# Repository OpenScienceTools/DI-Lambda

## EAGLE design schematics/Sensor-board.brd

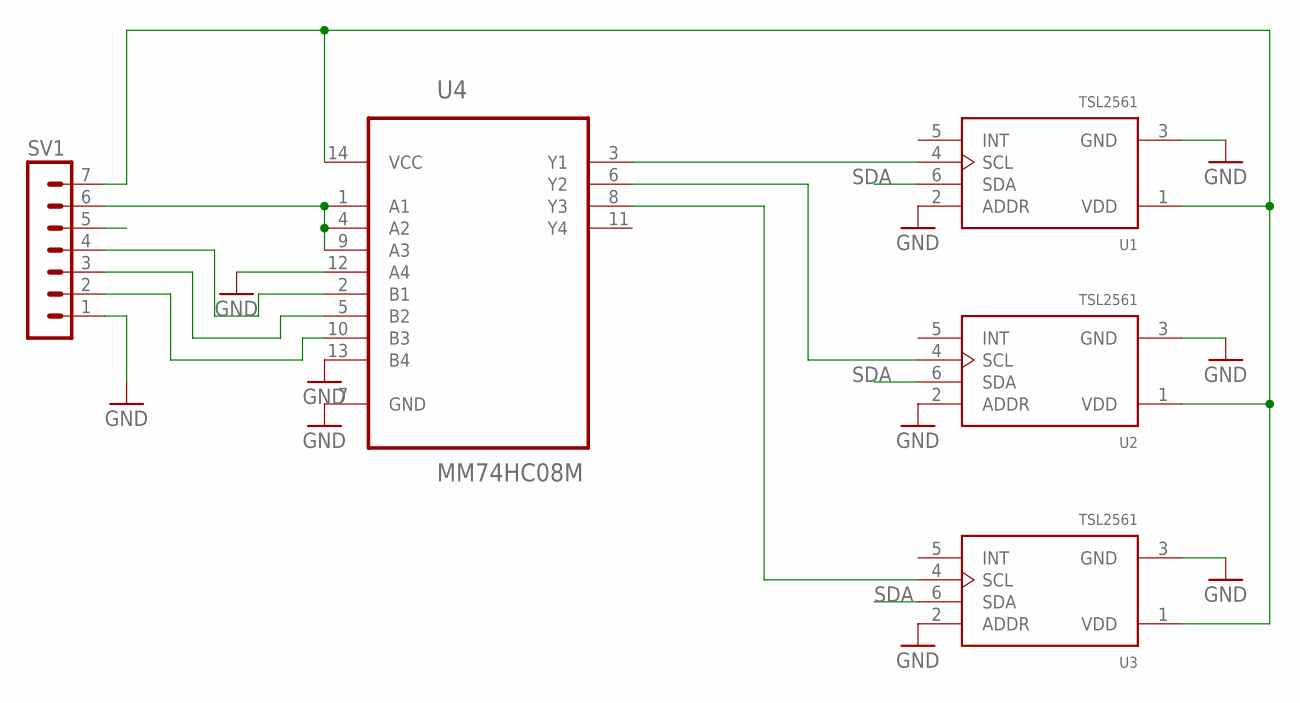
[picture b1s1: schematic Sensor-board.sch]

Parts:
SV1: MA07-1
U1, U2, U3: TSL2561; TMB-6
U4: MM74HC08M; SOIC127P600X175-14N

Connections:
GND: SV1.1, U1.2 (ADDR), U1.3 (GND), U2.2 (ADDR), U2.3 (GND), U3.2 (ADDR), U3.3 (GND), U4.7 (GND), U4.12 (A4), U4.13 (B4)
unnamed: U2.4 (SCL), U4.6 (Y2)
unnamed: U3.4 (SCL), U4.8 (Y3)
unnamed: U1.4 (SCL), U4.3 (Y1)
unnamed: SV1.4, U4.2 (B1)
unnamed: SV1.3, U4.5 (B2)
unnamed: SV1.2, U4.10 (B3)
SCL: SV1.6, U4.1 (A1), U4.4 (A2), U4.9 (A3)
SDA: SV1.5, U1.6 (SDA), U2.6 (SDA), U3.6 (SDA)
VCC: SV1.7, U1.1 (VDD), U2.1 (VDD), U3.1 (VDD), U4.14 (VCC)

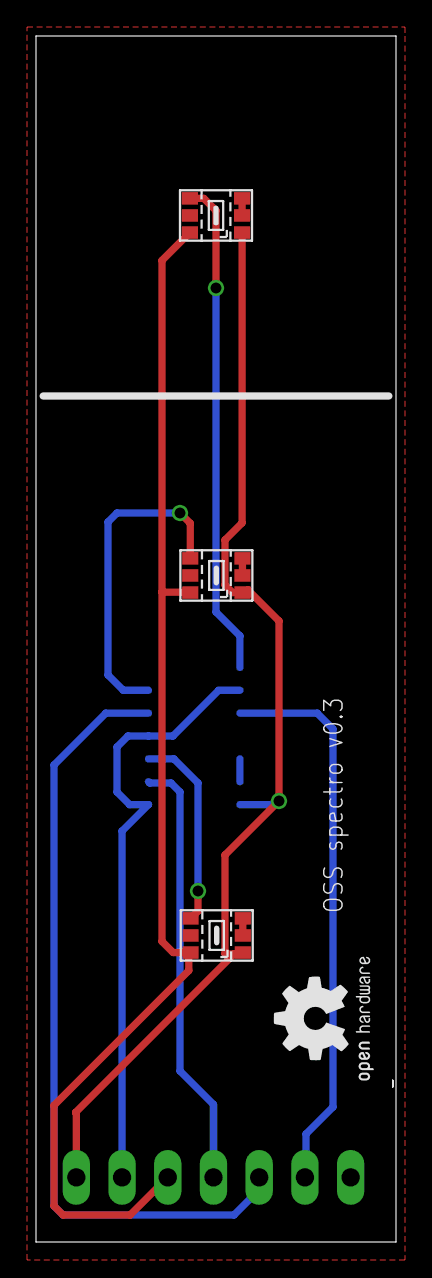
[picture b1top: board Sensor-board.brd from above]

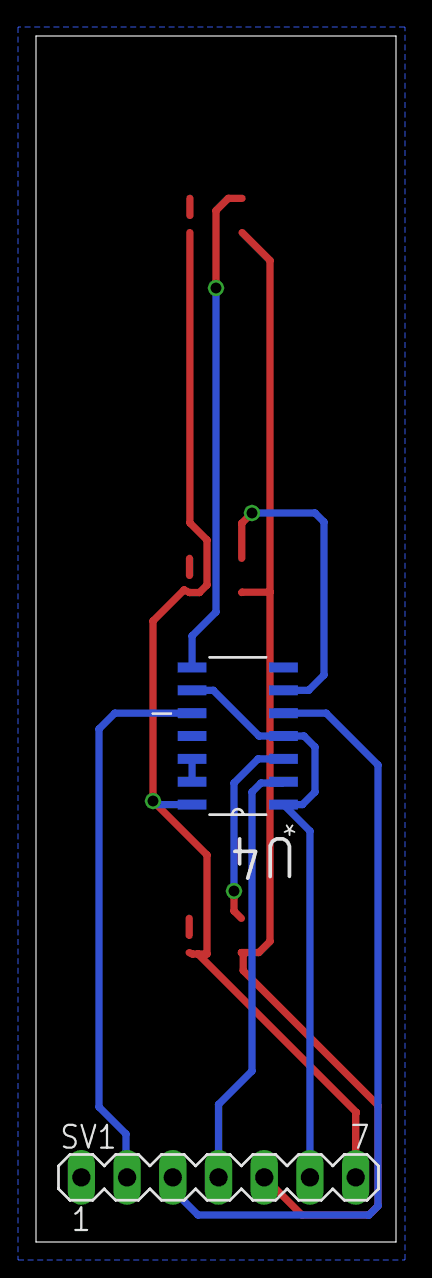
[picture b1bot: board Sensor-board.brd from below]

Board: 2 copper layers, 20.0 x 67.0 mm, 6 parts (2 on the bottom side), 10 nets.

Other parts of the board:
U$1: OSHW2

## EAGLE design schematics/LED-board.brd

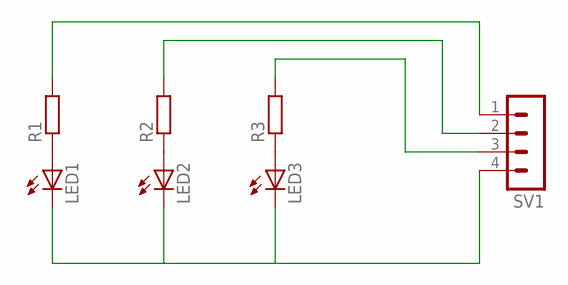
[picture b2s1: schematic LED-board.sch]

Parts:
LED1, LED2, LED3: LED5MM
R1, R2, R3: R0207/10; 0207/10
SV1: MA04-1

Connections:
GND: LED1.K (C), LED2.K (C), LED3.K (C), SV1.4
unnamed: LED1.A, R1.1
unnamed: LED2.A, R2.1
unnamed: LED3.A, R3.1
unnamed: R1.2, SV1.1
unnamed: R2.2, SV1.2
unnamed: R3.2, SV1.3

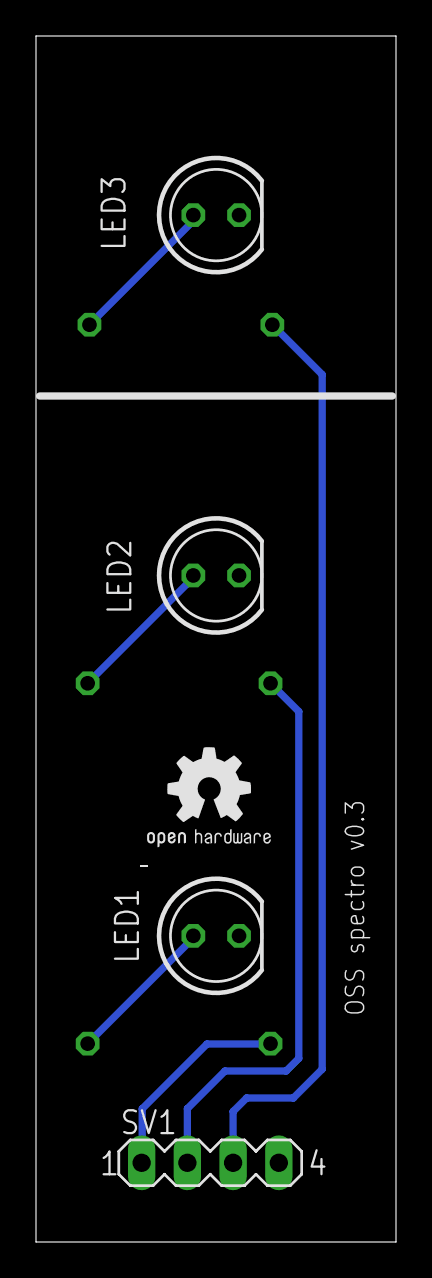
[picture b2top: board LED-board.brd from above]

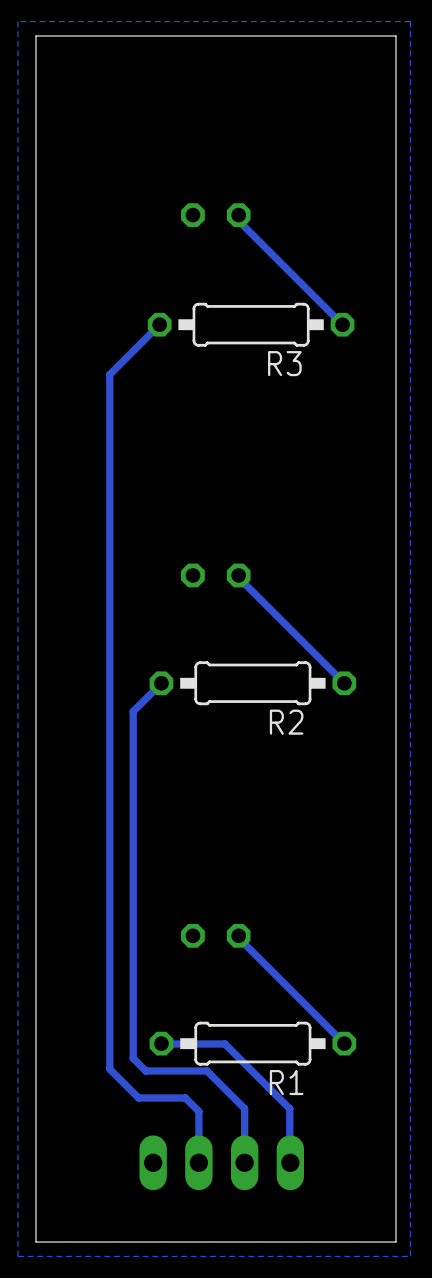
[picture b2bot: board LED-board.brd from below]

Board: 2 copper layers, 20.0 x 67.0 mm, 8 parts (3 on the bottom side), 7 nets.

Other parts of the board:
U$1: OSHW2

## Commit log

2014-12-25 Some unfinished schematics
2014-12-25 Add some unfinished parts
2014-12-25 Finish up the fist version, excluding the top part
2014-12-25 Render assembly
2014-12-25 Some progress with schematics
2014-12-25 Add stl exports for 3d printing
2014-12-25 Add pdf files for preview
2014-12-25 Add the top part of the box
2014-12-25 Some updates
2014-12-30 More detailed leds on the lead board
2014-12-30 Second version base part
2014-12-30 Second version of the top part
2014-12-30 stl export for the second version top part
2014-12-30 Add cuvette model
2014-12-31 Smaller motherboard, dimension changes to allow some gap betwen parts
2014-12-31 Add motherboard sketch to Render
2014-12-31 Add the cover part
2014-12-31 Accomodate top part for the cover
2014-12-31 Some changes here and there
2014-12-31 Some changes
2015-01-06 Reworked some schematics
2015-01-06 Rework bottom part to optimize size
2015-01-06 Bottom part sketch
2015-01-07 Actually add the base drender
2015-01-07 Finish the size rework
2015-01-11 Add assembly render pictures
2015-01-13 A last-minute commit before leaving for Grenoble
2015-02-03 New partially laser-cut version
2015-02-03 Add the laser-cut Autocad parts
2015-02-03 Just a quick fix
2015-06-03 Add the test rig, lots of other changes
2015-06-03 Spirulina prototype
2015-06-12 Start with the new slim design
2015-06-16 Some changes to parts used in the London event
2015-06-16 Add the distance test rig base
2015-06-16 Convert laser-cut parts to AI
2015-06-24 DI-Lambda Paris
2015-06-24 Align things to verify board dimensions
2015-06-29 DIL-Paris takes shape
2015-07-14 DI-Lambda Luna
2015-07-19 Steps towards a screwless case for DI-Lambda Paris
2015-07-19 Large git repo cleanup - move files around, remove unused
2015-07-19 Large git repo cleanup - update assemblies
2015-07-20 Spirulina: Add missing 1mm slit
2015-07-20 Paris: First attempt on screwless box
2015-07-21 Clean up the screwless box design
2015-08-01 Update screwless box design and rework the controller board
2015-08-05 Assemblies for each device, to make nice pictures
2015-08-07 Remove old schematics
2015-08-15 New slit inserts for the test rig
2015-08-19 All new schematics and boards
    - Reworked with KiCad
    - Includes:
    -- 2 Microcontroller board with Arduino Nano
    -- Microcontroller board with the Silabs EFM8UB10F8G MCU
    -- 1cm LED board
    -- 1cm sensor board with TSL2561
2015-08-20 schematics: update LED connections, use 4x resistor arrays
2016-03-11 Large amount of random changes
2016-05-24 Update the DI-Lambda Paris design: PCB pinholes, easier board removal, larger cuvette holes
2016-05-24 Add missing files for the nice-looking DI-Lambd Paris v2 version (cancelled)
2016-05-24 Add DI-Lambda v1 based on SZOMK AK-C-C10 profile (cancelled)
2016-05-24 Add DI-Lambda v1 based on SZOMK AK-C-C39 profile
2016-05-24 Schematics update
2016-05-24 DI-Lambda Paris: Fix core and box mismatches
2016-05-24 Schamatics: Add the pinhole board KiCad files
2016-07-03 Electronics update for V1
2016-07-03 Update V1 mechanical parts

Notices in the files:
parts and their libraries:
eagle-library-edeca.net-v5: This is v1 and is licensed under the Creative Commons (Attribution-Non-Commercial-Share Alike 2.0 UK)
